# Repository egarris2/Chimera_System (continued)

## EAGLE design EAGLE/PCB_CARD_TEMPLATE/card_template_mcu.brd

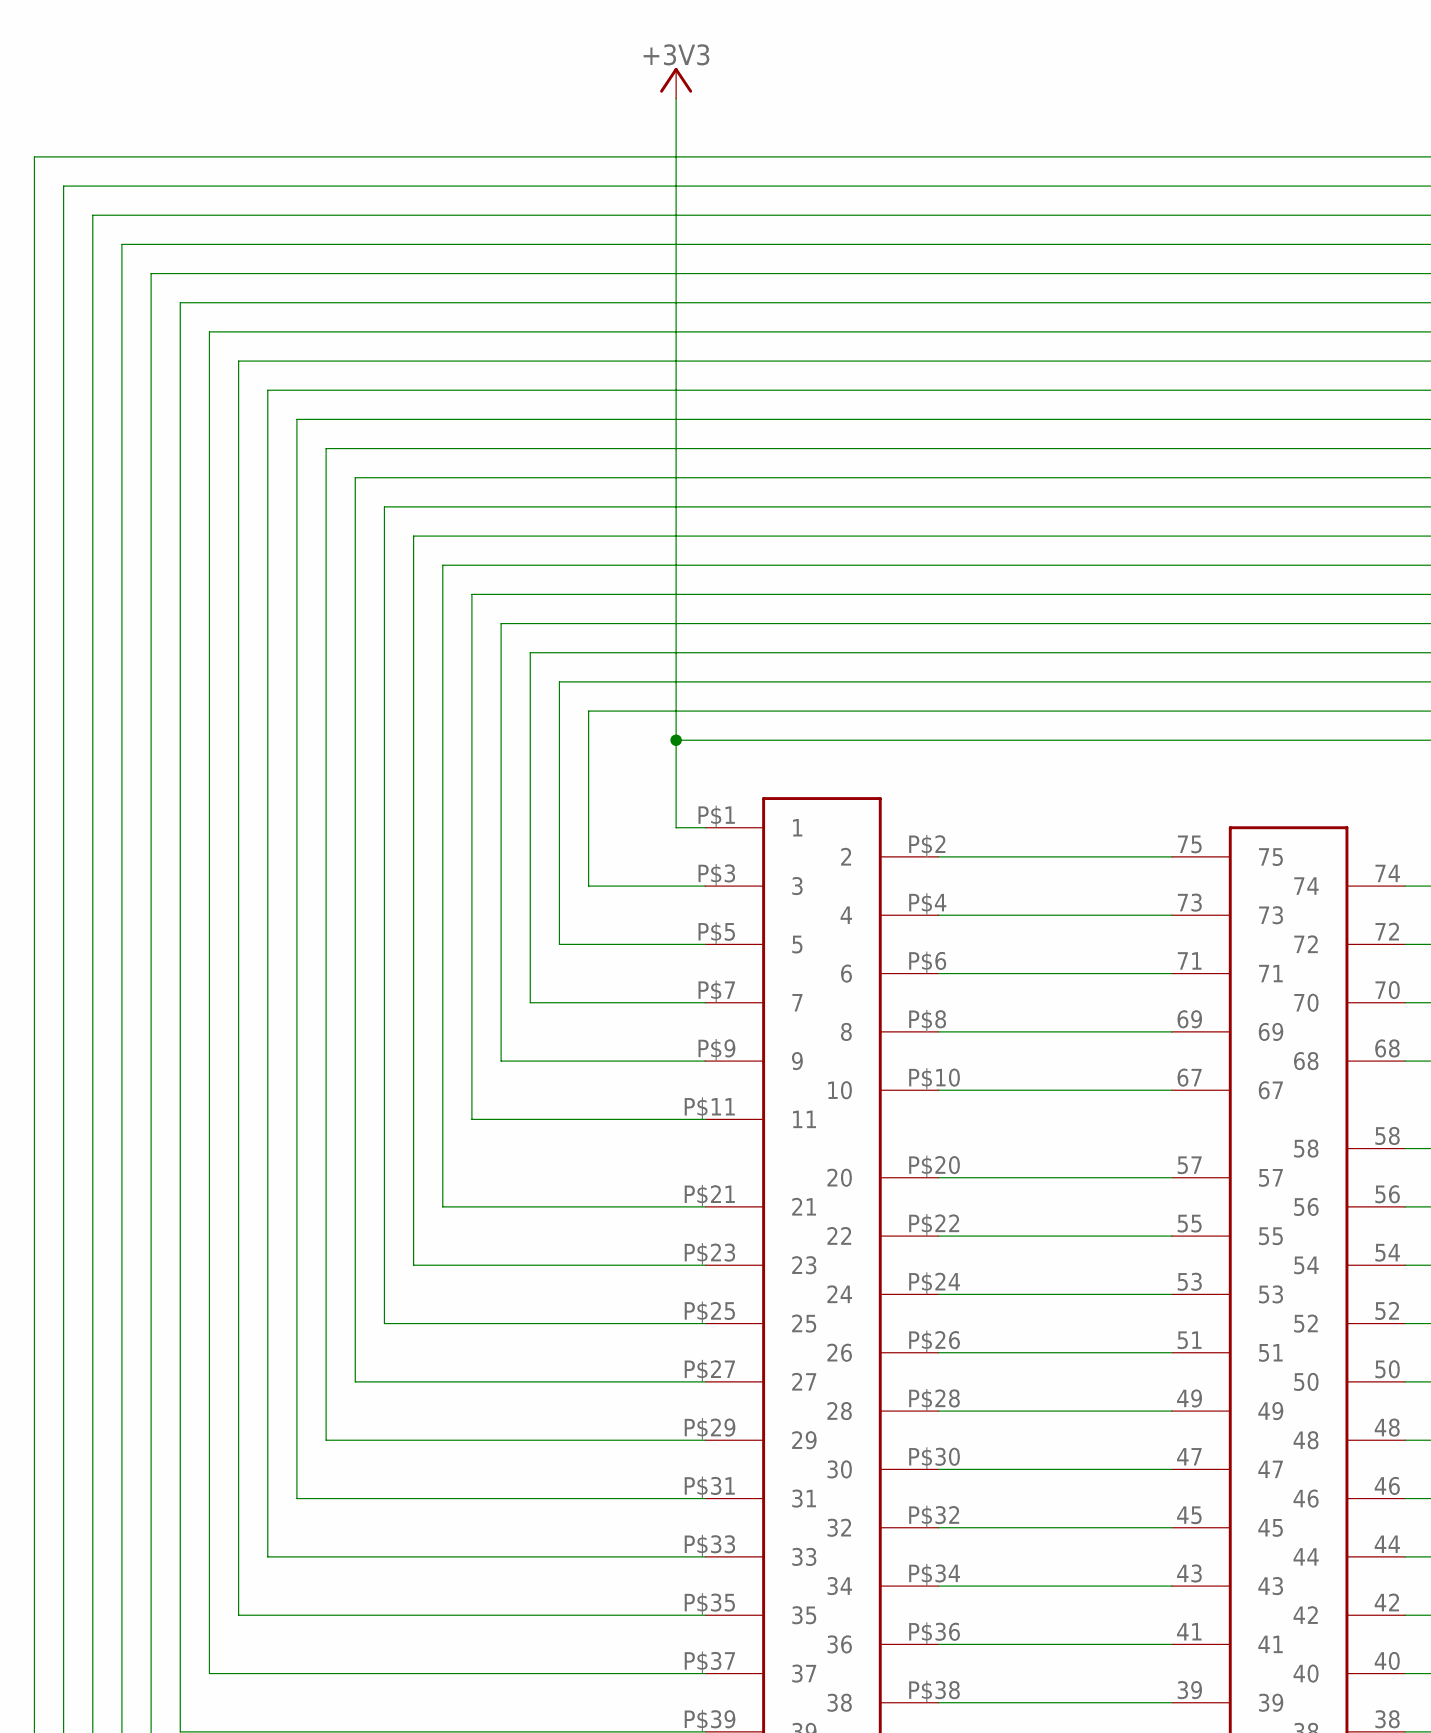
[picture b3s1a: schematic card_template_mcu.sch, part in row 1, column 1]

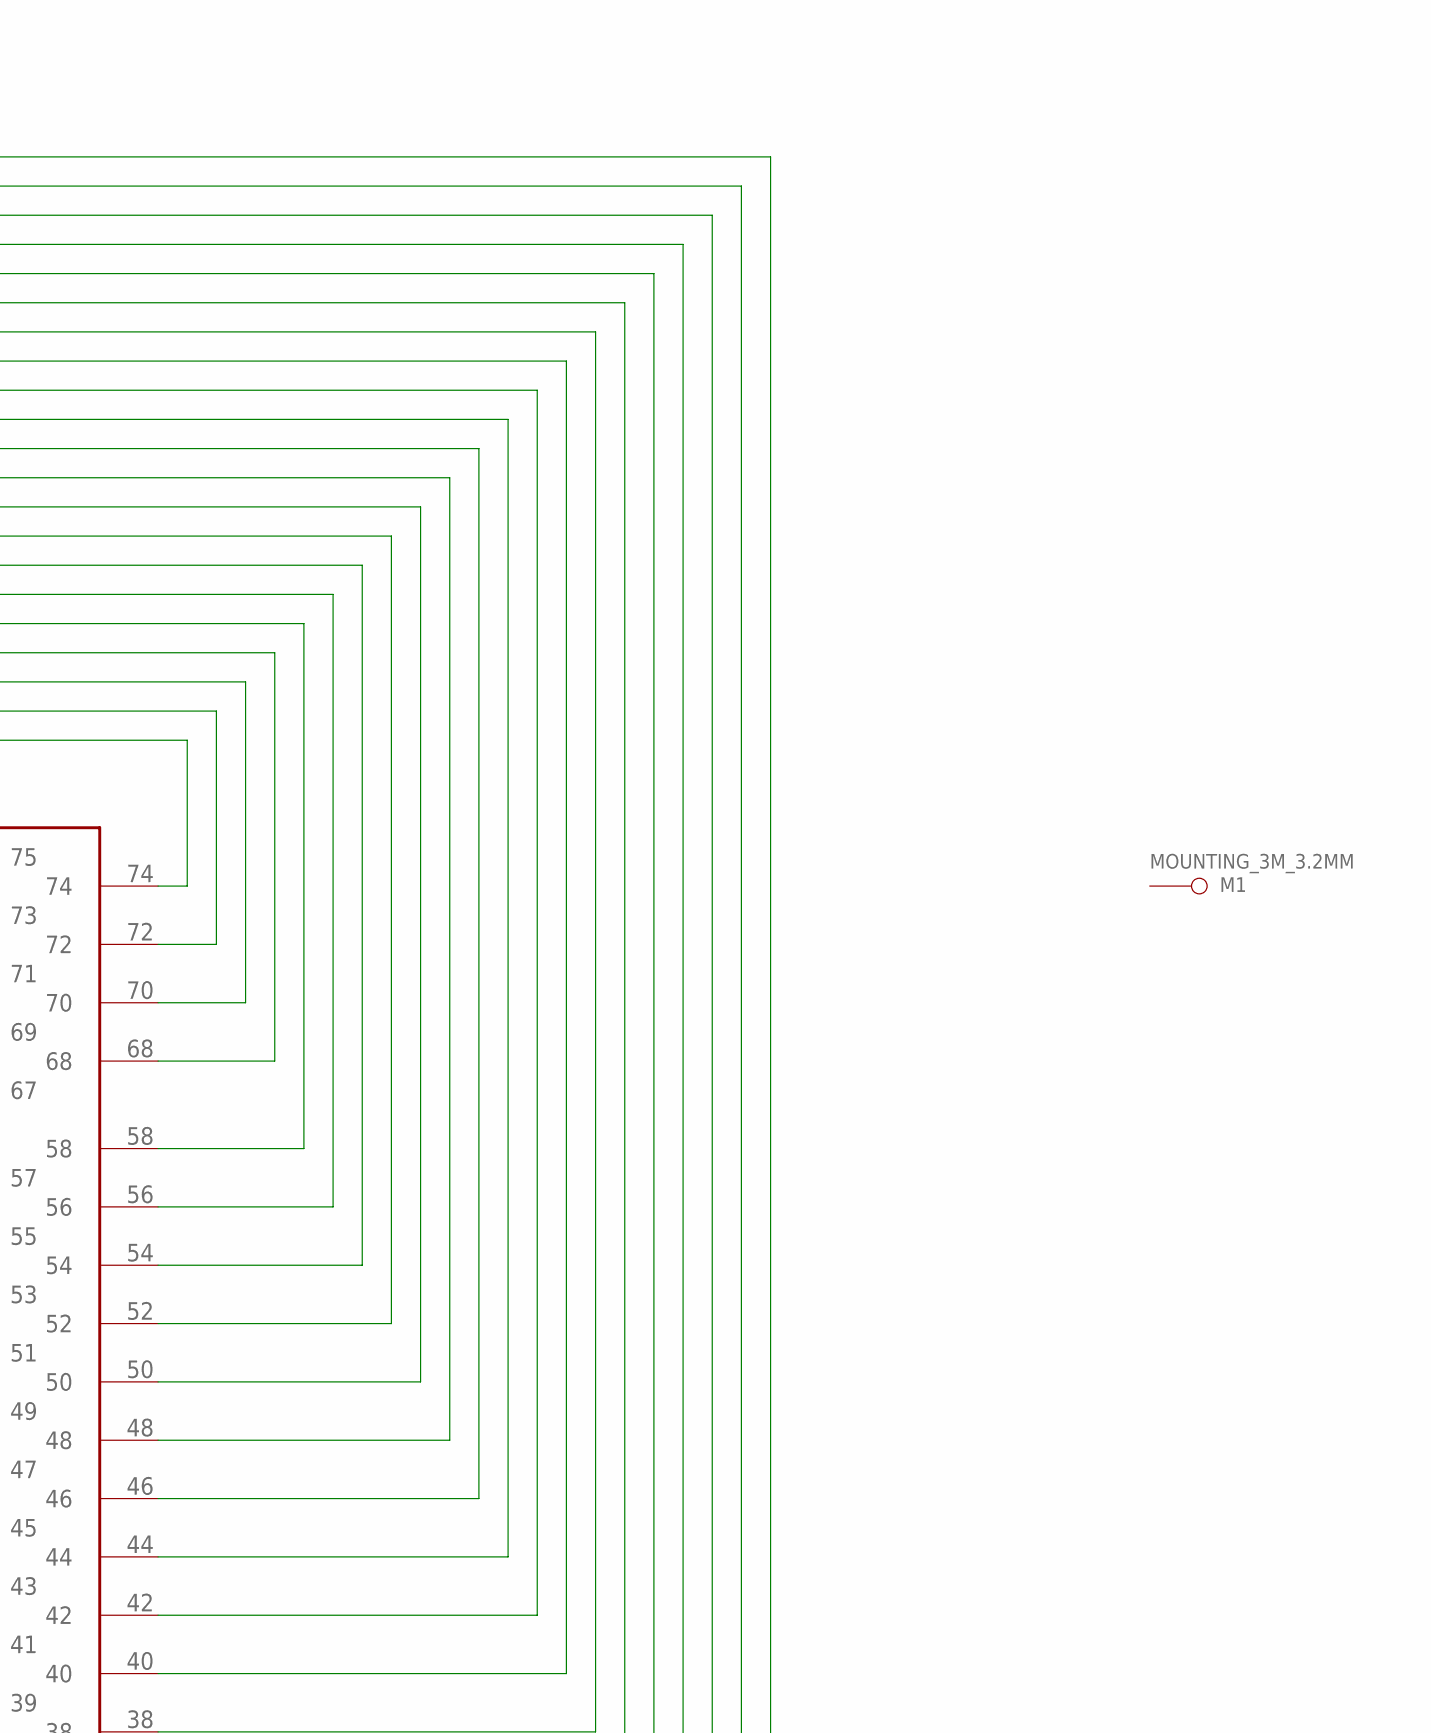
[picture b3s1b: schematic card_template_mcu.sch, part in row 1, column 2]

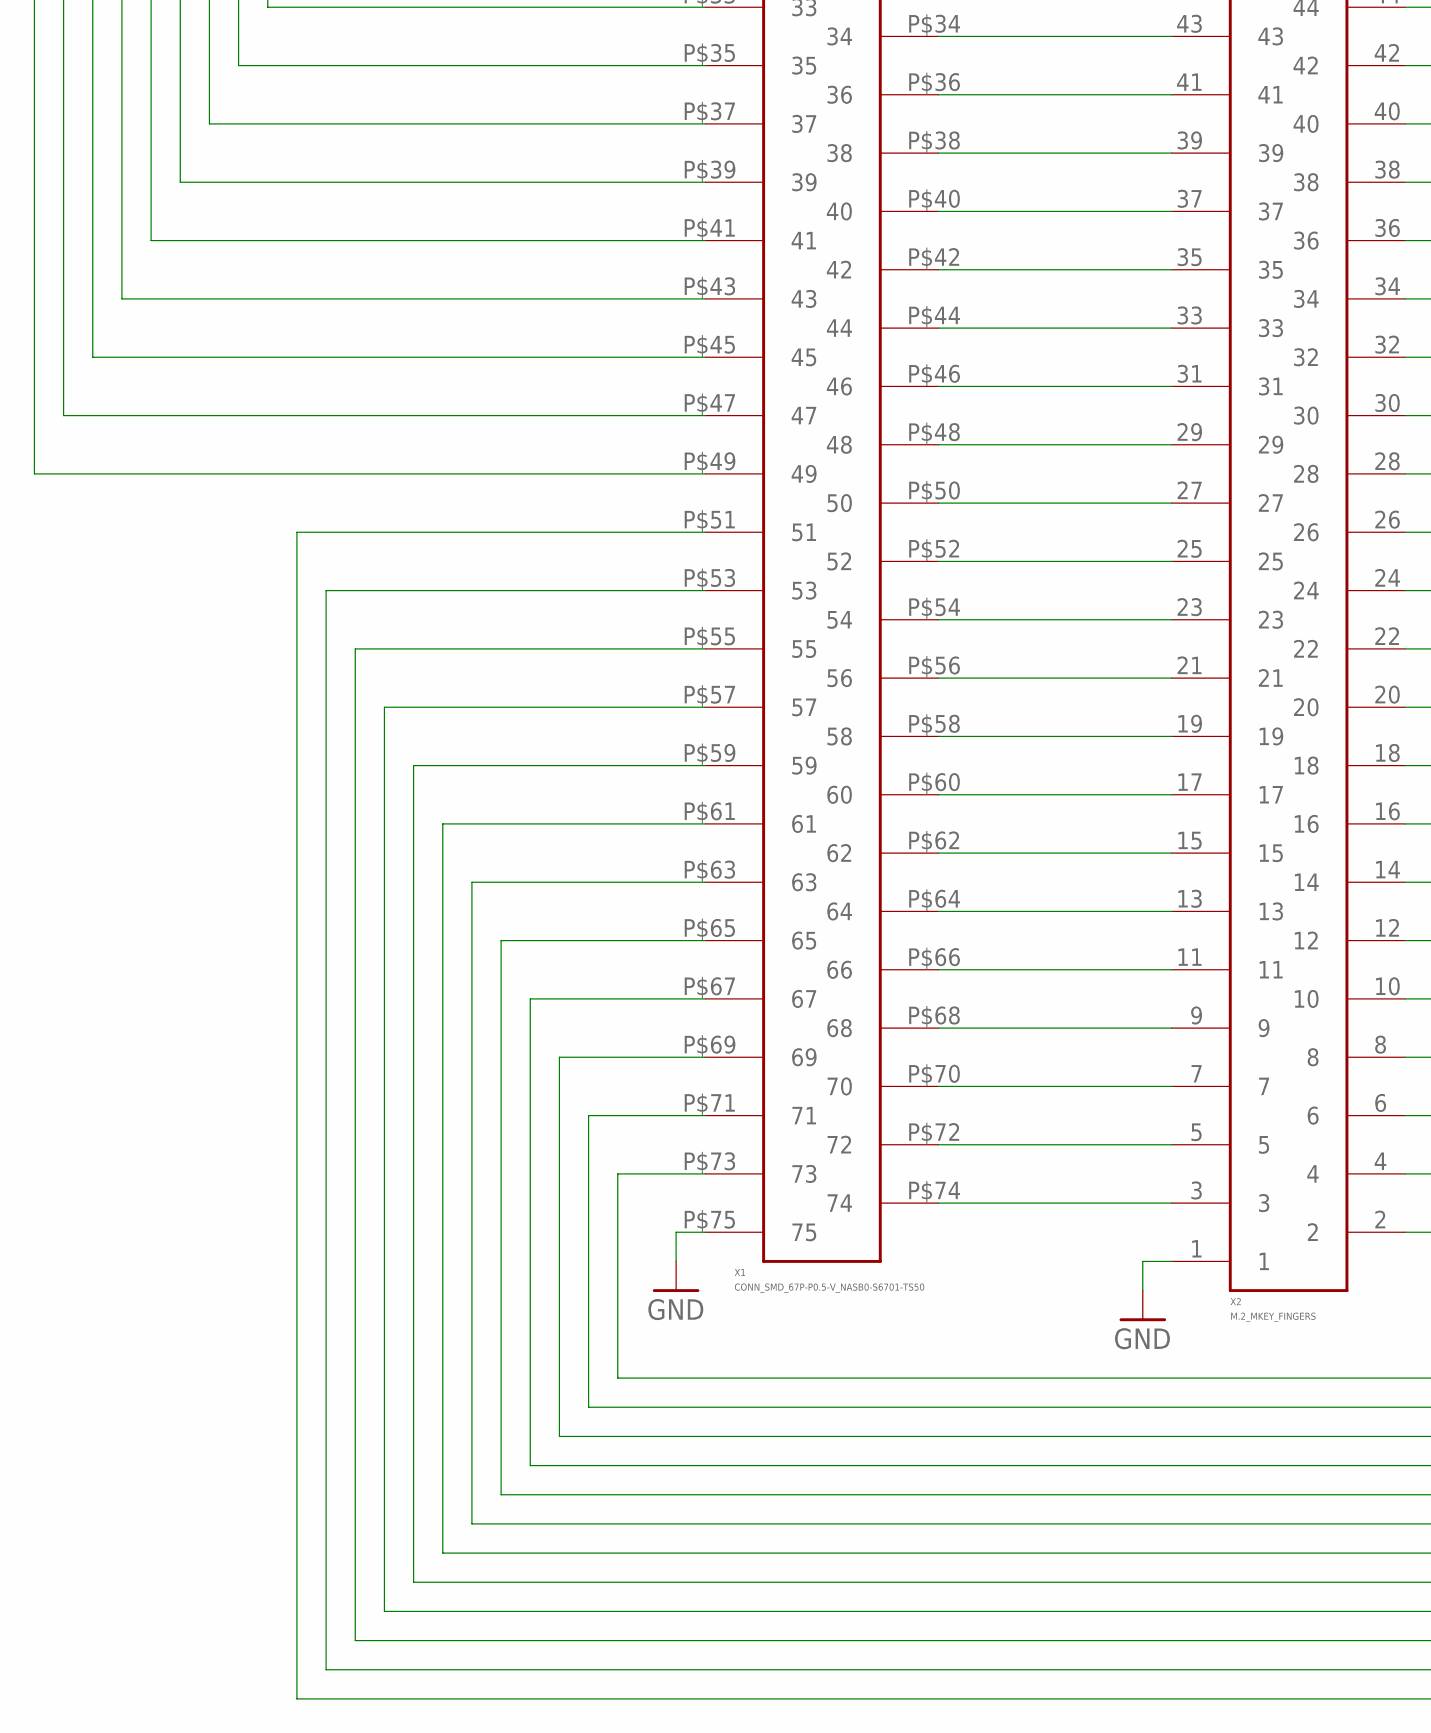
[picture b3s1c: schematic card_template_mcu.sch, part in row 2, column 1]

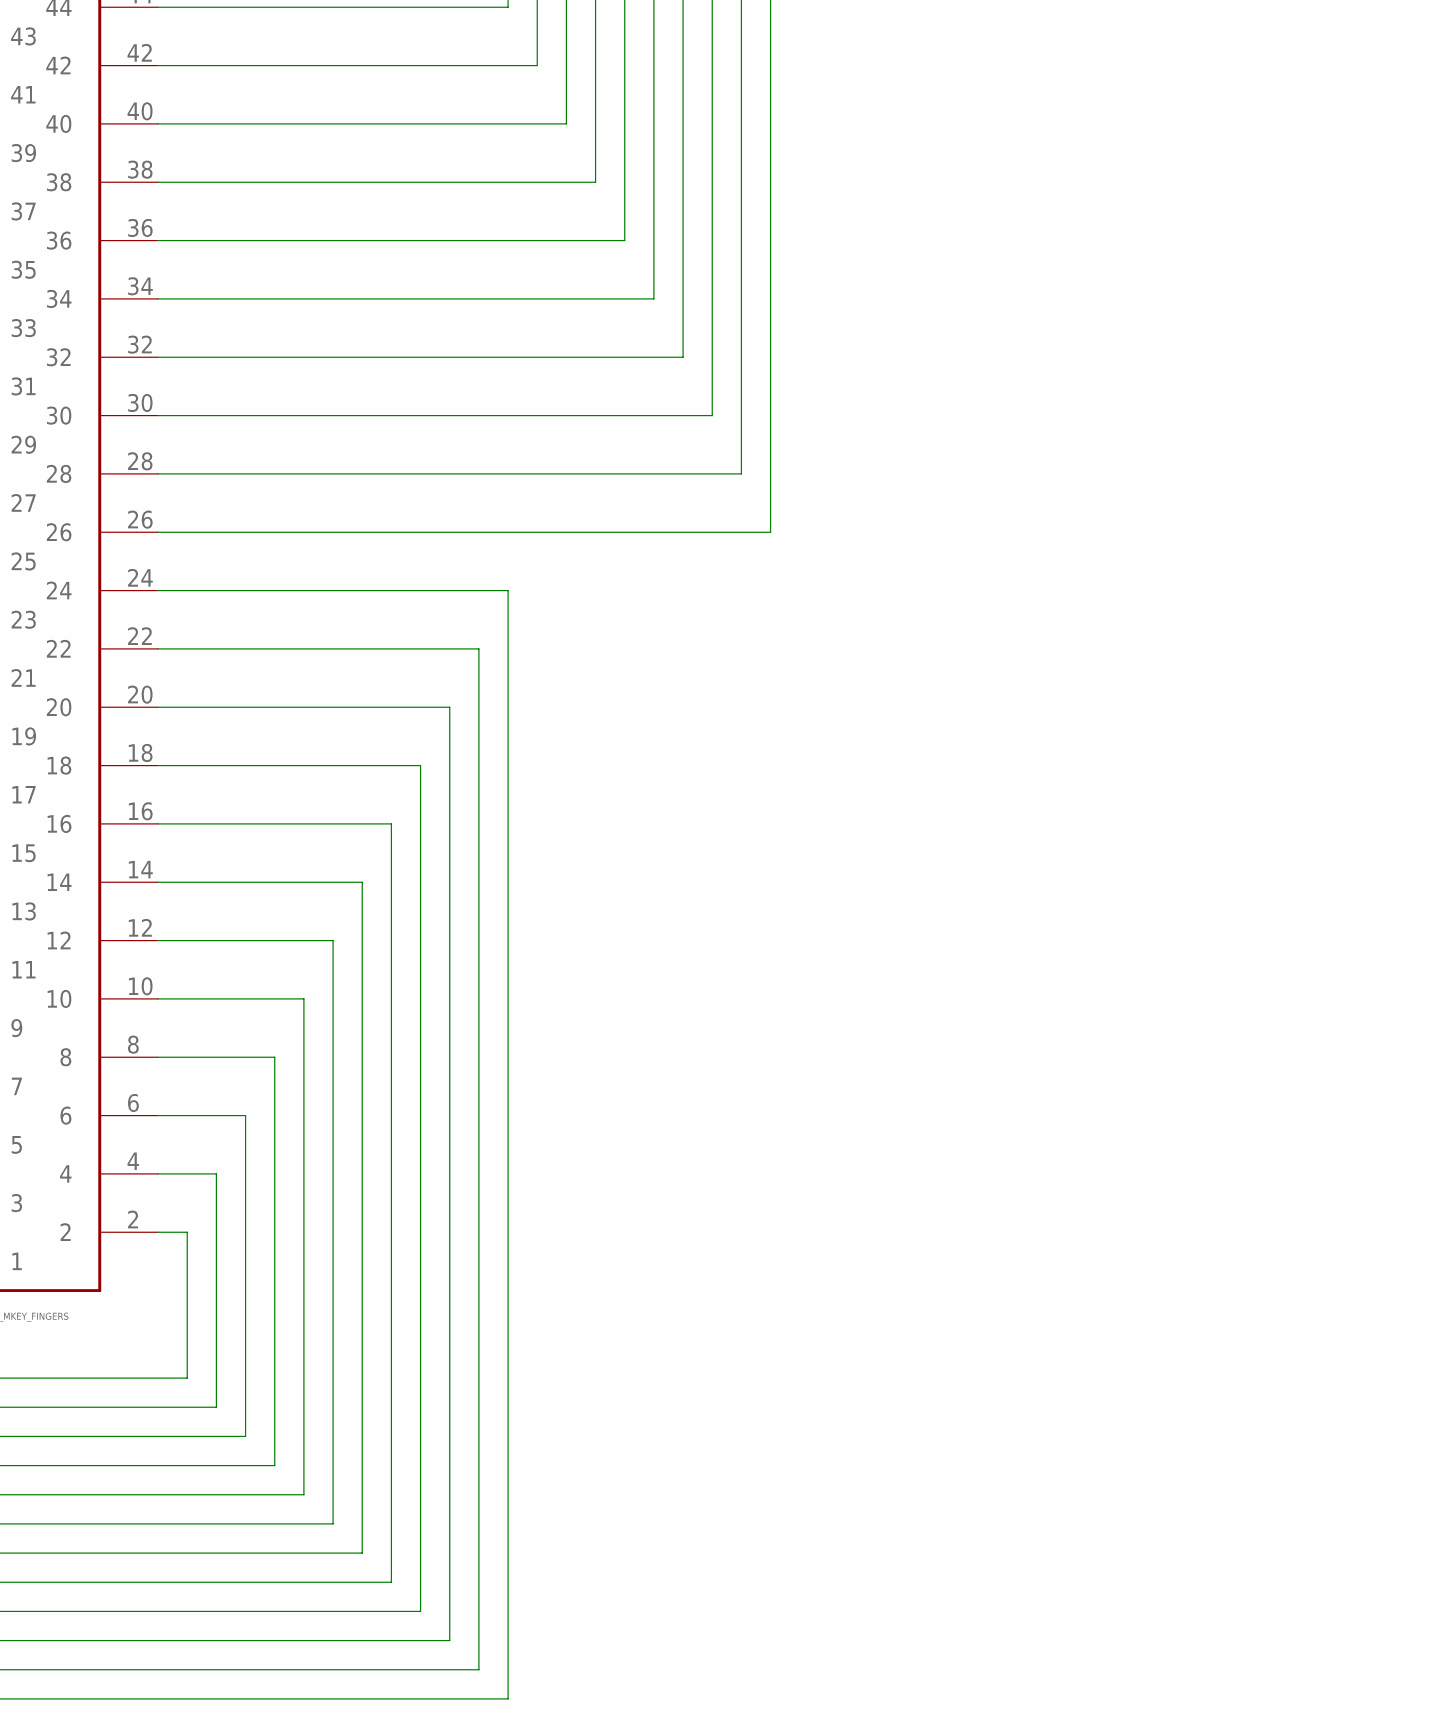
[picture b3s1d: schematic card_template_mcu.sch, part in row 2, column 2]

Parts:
M1: MOUNTING_3M_3.2MM
X1: CONN_SMD_67P-P0.5-V_NASB0-S6701-TS50
X2: M.2_MKEY_FINGERS

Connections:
+3V3: X1.P$1 (1), X2.74
GND: X1.P$75 (75), X2.1
unnamed: X1.P$23 (23), X2.52
unnamed: X1.P$25 (25), X2.50
unnamed: X1.P$73 (73), X2.2
unnamed: X1.P$71 (71), X2.4
unnamed: X1.P$69 (69), X2.6
unnamed: X1.P$67 (67), X2.8
unnamed: X1.P$65 (65), X2.10
unnamed: X1.P$63 (63), X2.12
unnamed: X1.P$61 (61), X2.14
unnamed: X1.P$59 (59), X2.16
unnamed: X1.P$57 (57), X2.18
unnamed: X1.P$55 (55), X2.20
unnamed: X1.P$53 (53), X2.22
unnamed: X1.P$51 (51), X2.24
unnamed: X1.P$21 (21), X2.54
unnamed: X1.P$27 (27), X2.48
unnamed: X1.P$29 (29), X2.46
unnamed: X1.P$31 (31), X2.44
unnamed: X1.P$33 (33), X2.42
unnamed: X1.P$35 (35), X2.40
unnamed: X1.P$37 (37), X2.38
unnamed: X1.P$39 (39), X2.36
unnamed: X1.P$41 (41), X2.34
unnamed: X1.P$43 (43), X2.32
unnamed: X1.P$45 (45), X2.30
unnamed: X1.P$47 (47), X2.28
unnamed: X1.P$49 (49), X2.26
unnamed: X1.P$11 (11), X2.56
unnamed: X1.P$9 (9), X2.58
unnamed: X1.P$7 (7), X2.68
unnamed: X1.P$5 (5), X2.70
unnamed: X1.P$3 (3), X2.72
unnamed: X1.P$2 (2), X2.75
unnamed: X1.P$22 (22), X2.55
unnamed: X1.P$4 (4), X2.73
unnamed: X1.P$6 (6), X2.71
unnamed: X1.P$8 (8), X2.69
unnamed: X1.P$10 (10), X2.67
unnamed: X1.P$20 (20), X2.57
unnamed: X1.P$24 (24), X2.53
unnamed: X1.P$26 (26), X2.51
unnamed: X1.P$28 (28), X2.49
unnamed: X1.P$30 (30), X2.47
unnamed: X1.P$32 (32), X2.45
unnamed: X1.P$34 (34), X2.43
unnamed: X1.P$36 (36), X2.41
unnamed: X1.P$38 (38), X2.39
unnamed: X1.P$40 (40), X2.37
unnamed: X1.P$42 (42), X2.35
unnamed: X1.P$44 (44), X2.33
unnamed: X1.P$74 (74), X2.3
unnamed: X1.P$72 (72), X2.5
unnamed: X1.P$70 (70), X2.7
unnamed: X1.P$68 (68), X2.9
unnamed: X1.P$66 (66), X2.11
unnamed: X1.P$64 (64), X2.13
unnamed: X1.P$62 (62), X2.15
unnamed: X1.P$60 (60), X2.17
unnamed: X1.P$58 (58), X2.19
unnamed: X1.P$56 (56), X2.21
unnamed: X1.P$54 (54), X2.23
unnamed: X1.P$52 (52), X2.25
unnamed: X1.P$46 (46), X2.31
unnamed: X1.P$48 (48), X2.29
unnamed: X1.P$50 (50), X2.27

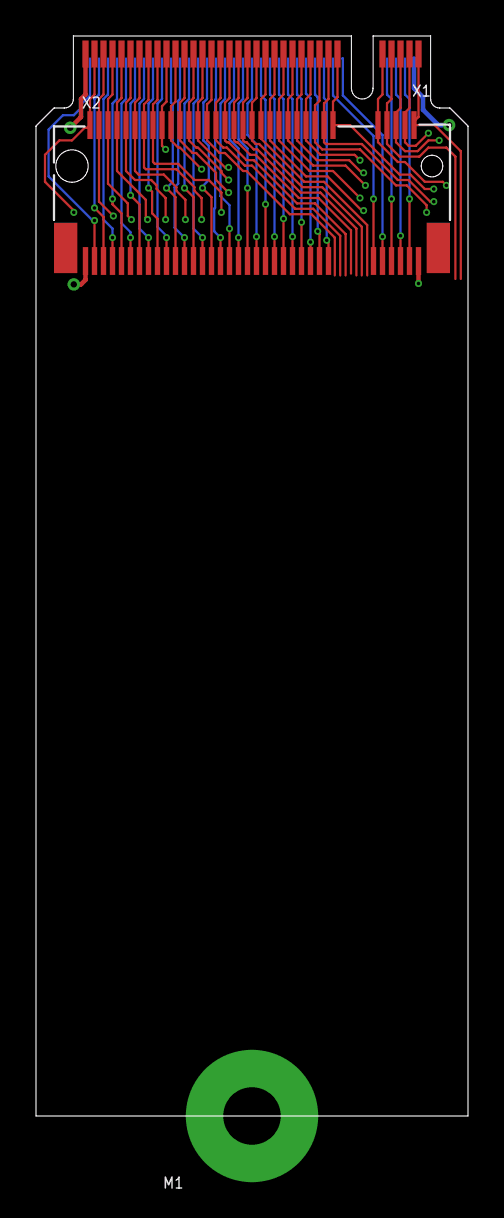
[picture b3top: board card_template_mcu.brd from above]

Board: 4 copper layers, 24.0 x 60.0 mm, 3 parts (0 on the bottom side), 67 nets.

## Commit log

2023-10-11 First commit. WORK IN PROGRESS
2023-10-11 Added image with annotations.
2023-10-11 Cleaned up folders
2023-10-11 Added Nimean Pin description document
2023-10-12 added Kicad JLC workflow document
2023-10-12 start eagle port
2023-10-12 ignore
2023-10-13 have footprints complete
2023-10-17 added board settings, including design rules, to the accessory card template board file.
2023-10-17 completed accessory card template
2023-10-18 finish mcu card template
2023-10-18 Connected air wire on pad 47 of the card_template
2023-10-18 Moved board into title block border. for Chimera_Card_template
2023-10-18 start pic24 card
2023-10-19 finished breaking out pic pins up near connector
2023-10-19 cleaned up model_chimera_card_holder folder and updated card holder model.
2023-10-19 pic24 card is done, gerbers and jlc files generated
2023-10-23 upd gitignore
2023-10-23 finish pwr supply card
2023-11-16 Backlink to CADLAB.io has been added.
